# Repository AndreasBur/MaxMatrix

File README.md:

# MaxMatrix
This is a Arduino library for the MAX7219 and a LED dot matrix.

Features:

- set Char
- scroll text over the matrix
- set dot

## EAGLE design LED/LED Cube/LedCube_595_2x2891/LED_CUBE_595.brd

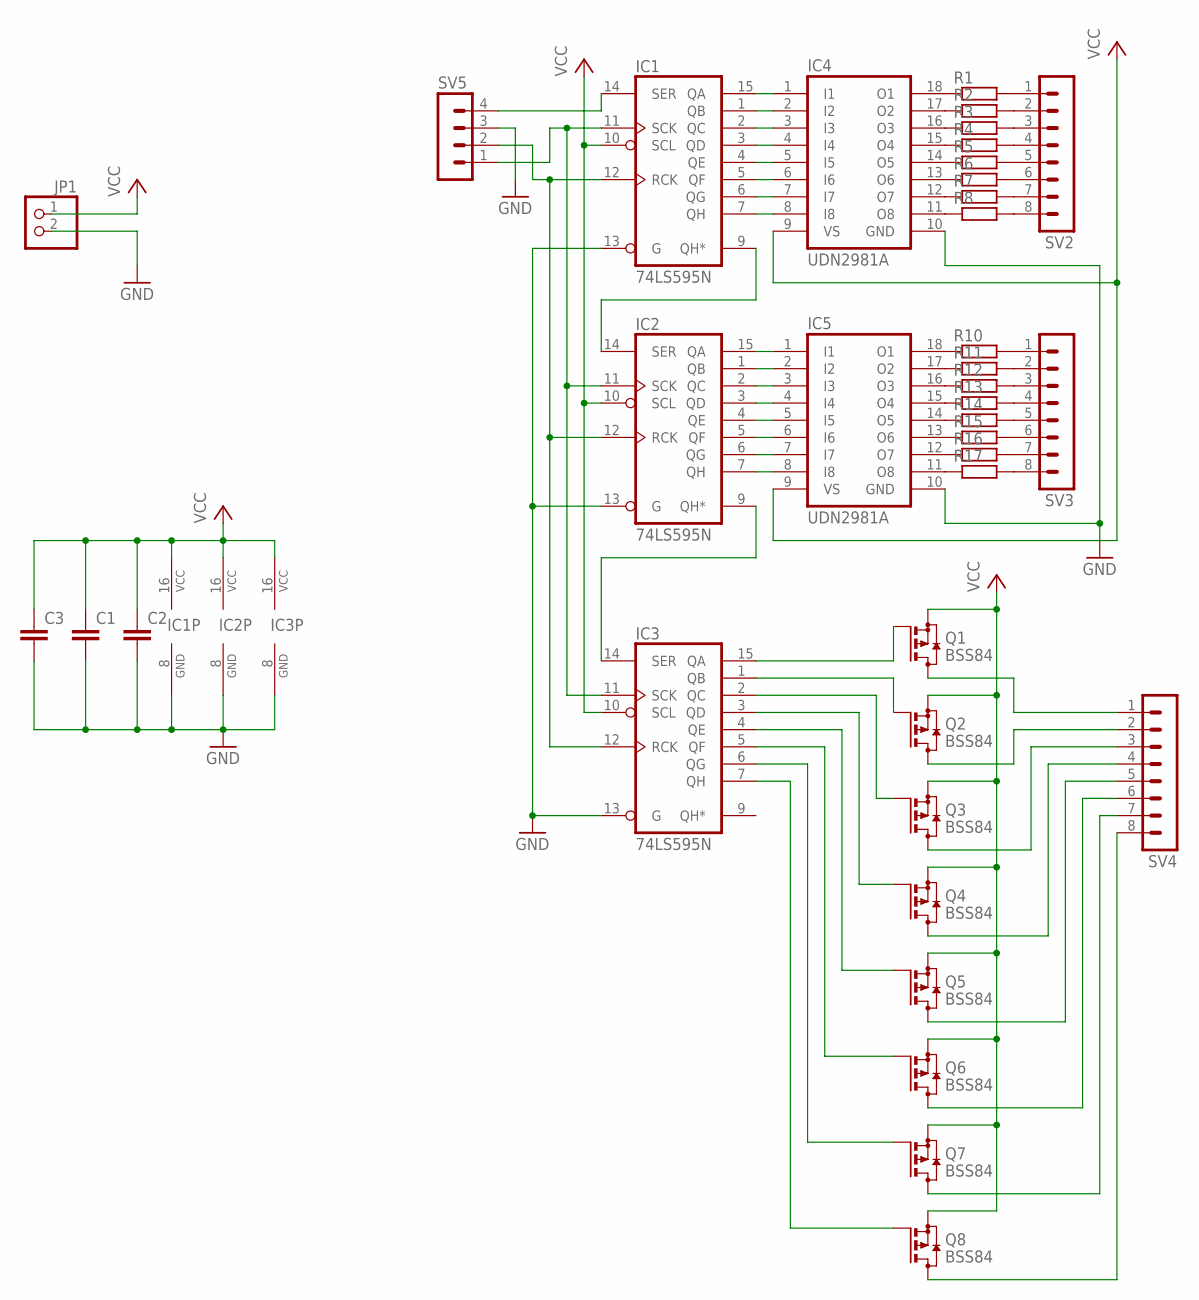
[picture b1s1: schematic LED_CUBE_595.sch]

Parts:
C1, C2, C3: C-EU025-025X050; C025-025X050
IC1, IC2, IC3: 74LS595N; DIL16
IC4, IC5: UDN2981A; DIL18
JP1: PINHD-1X2; 1X02
Q1, Q2, Q3, Q4, Q5, Q6, Q7, Q8: BSS84; SOT23
R1, R2, R3, R4, R5, R6, R7, R8, R10, R11, R12, R13, R14, R15, R16, R17: R-EU_0204/2V; 0204V
SV2, SV3, SV4: MA08-1
SV5: MA04-1

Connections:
GND: C1.2, C2.2, C3.2, IC1.8 (GND), IC1.13 (G), IC2.8 (GND), IC2.13 (G), IC3.8 (GND), IC3.13 (G), IC4.10 (GND), IC5.10 (GND), JP1.2, SV5.3
unnamed: IC1.9 (QH*), IC2.14 (SER)
unnamed: IC1.15 (QA), IC4.1 (I1)
unnamed: IC1.1 (QB), IC4.2 (I2)
unnamed: IC1.2 (QC), IC4.3 (I3)
unnamed: IC1.3 (QD), IC4.4 (I4)
unnamed: IC1.4 (QE), IC4.5 (I5)
unnamed: IC1.5 (QF), IC4.6 (I6)
unnamed: IC1.6 (QG), IC4.7 (I7)
unnamed: IC1.7 (QH), IC4.8 (I8)
unnamed: IC2.15 (QA), IC5.1 (I1)
unnamed: IC2.1 (QB), IC5.2 (I2)
unnamed: IC2.2 (QC), IC5.3 (I3)
unnamed: IC2.3 (QD), IC5.4 (I4)
unnamed: IC2.4 (QE), IC5.5 (I5)
unnamed: IC2.5 (QF), IC5.6 (I6)
unnamed: IC2.6 (QG), IC5.7 (I7)
unnamed: IC2.7 (QH), IC5.8 (I8)
unnamed: IC4.18 (O1), R1.1
unnamed: IC4.17 (O2), R2.1
unnamed: IC4.16 (O3), R3.1
unnamed: IC4.15 (O4), R4.1
unnamed: IC4.14 (O5), R5.1
unnamed: IC4.13 (O6), R6.1
unnamed: IC4.12 (O7), R7.1
unnamed: IC4.11 (O8), R8.1
unnamed: R1.2, SV2.1
unnamed: IC1.11 (SCK), IC2.11 (SCK), IC3.11 (SCK), SV5.1
unnamed: IC1.14 (SER), SV5.4
unnamed: IC1.12 (RCK), IC2.12 (RCK), IC3.12 (RCK), SV5.2
unnamed: IC2.9 (QH*), IC3.14 (SER)
unnamed: IC5.17 (O2), R11.1
unnamed: IC5.16 (O3), R12.1
unnamed: IC5.15 (O4), R13.1
unnamed: IC5.14 (O5), R14.1
unnamed: IC5.13 (O6), R15.1
unnamed: IC5.12 (O7), R16.1
unnamed: IC5.11 (O8), R17.1
unnamed: R2.2, SV2.2
unnamed: IC5.18 (O1), R10.1
unnamed: R3.2, SV2.3
unnamed: R4.2, SV2.4
unnamed: R5.2, SV2.5
unnamed: R6.2, SV2.6
unnamed: R7.2, SV2.7
unnamed: R8.2, SV2.8
unnamed: R10.2, SV3.1
unnamed: R11.2, SV3.2
unnamed: R12.2, SV3.3
unnamed: R13.2, SV3.4
unnamed: R14.2, SV3.5
unnamed: R15.2, SV3.6
unnamed: R16.2, SV3.7
unnamed: R17.2, SV3.8
unnamed: Q1.3 (D), SV4.1
unnamed: Q2.3 (D), SV4.2
unnamed: Q3.3 (D), SV4.3
unnamed: Q4.3 (D), SV4.4
unnamed: Q5.3 (D), SV4.5
unnamed: Q6.3 (D), SV4.6
unnamed: Q7.3 (D), SV4.7
unnamed: Q8.3 (D), SV4.8
unnamed: IC3.1 (QB), Q2.1 (G)
unnamed: IC3.2 (QC), Q3.1 (G)
unnamed: IC3.3 (QD), Q4.1 (G)
unnamed: IC3.4 (QE), Q5.1 (G)
unnamed: IC3.5 (QF), Q6.1 (G)
unnamed: IC3.6 (QG), Q7.1 (G)
unnamed: IC3.7 (QH), Q8.1 (G)
unnamed: IC3.15 (QA), Q1.1 (G)
VCC: C1.1, C2.1, C3.1, IC1.10 (SCL), IC1.16 (VCC), IC2.10 (SCL), IC2.16 (VCC), IC3.10 (SCL), IC3.16 (VCC), IC4.9 (VS), IC5.9 (VS), JP1.1, Q1.2 (S), Q2.2 (S), Q3.2 (S), Q4.2 (S), Q5.2 (S), Q6.2 (S), Q7.2 (S), Q8.2 (S)

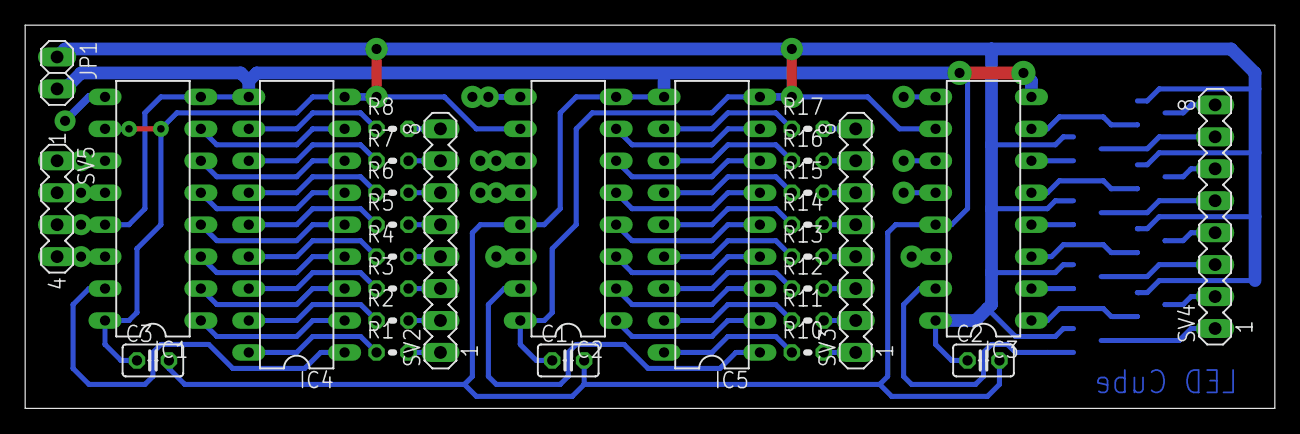
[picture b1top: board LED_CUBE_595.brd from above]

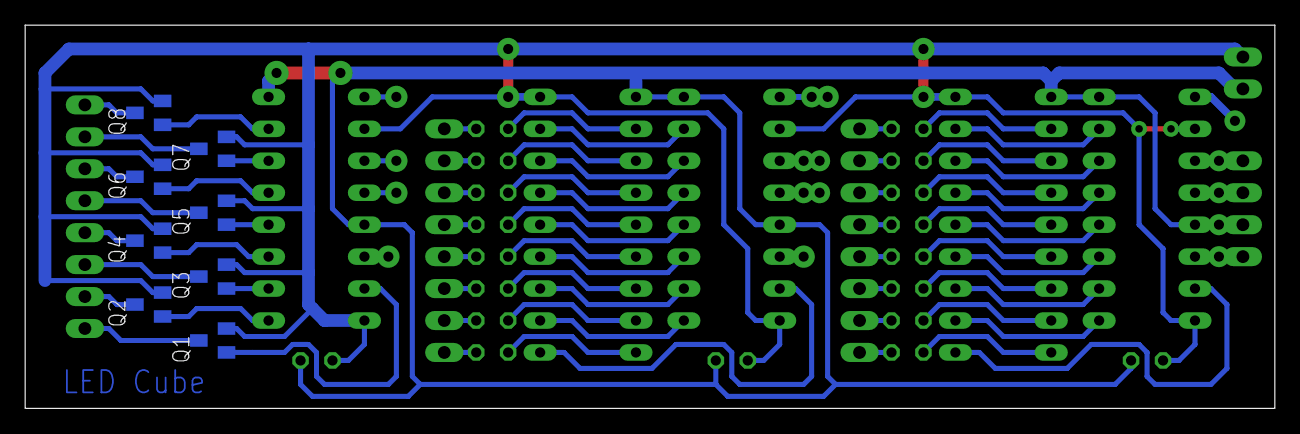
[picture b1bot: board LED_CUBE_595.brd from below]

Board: 2 copper layers, 99.4 x 30.5 mm, 37 parts (8 on the bottom side), 71 nets.

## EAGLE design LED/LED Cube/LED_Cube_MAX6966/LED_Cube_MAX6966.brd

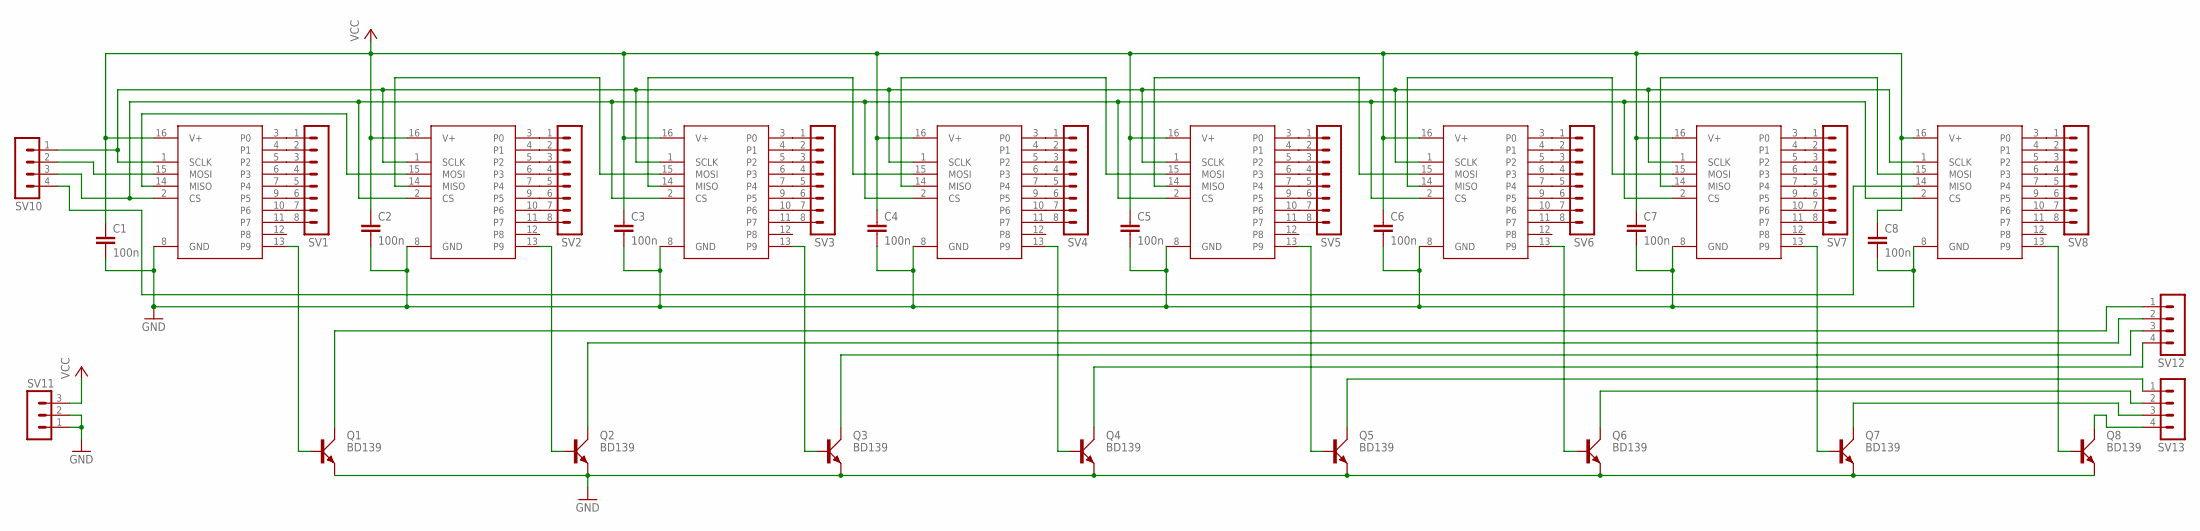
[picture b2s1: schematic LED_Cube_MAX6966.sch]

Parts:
C1, C2, C3, C4, C5, C6, C7, C8: 100n; C025_050-025X075
Q1, Q2, Q3, Q4, Q5, Q6, Q7, Q8: BD139; TO126AV
SV1, SV2, SV3, SV4, SV5, SV6, SV7, SV8: MA08-1
SV10, SV12, SV13: MA04-1
SV11: MA03-1
U$1, U$2, U$3, U$4, U$5, U$6, U$7, U$8: MAX6966; QSOP16

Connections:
GND: C1.2, C2.2, C3.2, C4.2, C5.2, C6.2, C7.2, C8.2, Q1.E, Q2.E, Q3.E, Q4.E, Q5.E, Q6.E, Q7.E, Q8.E, SV11.1, SV11.2, U$1.8 (GND), U$2.8 (GND), U$3.8 (GND), U$4.8 (GND), U$5.8 (GND), U$6.8 (GND), U$7.8 (GND), U$8.8 (GND)
unnamed: SV1.1, U$1.3 (P0)
unnamed: SV1.2, U$1.4 (P1)
unnamed: SV1.3, U$1.5 (P2)
unnamed: SV1.4, U$1.6 (P3)
unnamed: SV1.5, U$1.7 (P4)
unnamed: SV1.6, U$1.9 (P5)
unnamed: SV1.7, U$1.10 (P6)
unnamed: SV1.8, U$1.11 (P7)
unnamed: SV2.1, U$2.3 (P0)
unnamed: SV2.2, U$2.4 (P1)
unnamed: SV2.3, U$2.5 (P2)
unnamed: SV2.4, U$2.6 (P3)
unnamed: SV2.5, U$2.7 (P4)
unnamed: SV2.6, U$2.9 (P5)
unnamed: SV2.7, U$2.10 (P6)
unnamed: SV2.8, U$2.11 (P7)
unnamed: SV3.1, U$3.3 (P0)
unnamed: SV3.2, U$3.4 (P1)
unnamed: SV3.3, U$3.5 (P2)
unnamed: SV3.4, U$3.6 (P3)
unnamed: SV3.5, U$3.7 (P4)
unnamed: SV3.6, U$3.9 (P5)
unnamed: SV3.7, U$3.10 (P6)
unnamed: SV3.8, U$3.11 (P7)
unnamed: SV4.1, U$4.3 (P0)
unnamed: SV4.2, U$4.4 (P1)
unnamed: SV4.3, U$4.5 (P2)
unnamed: SV4.4, U$4.6 (P3)
unnamed: SV4.5, U$4.7 (P4)
unnamed: SV4.6, U$4.9 (P5)
unnamed: SV4.7, U$4.10 (P6)
unnamed: SV4.8, U$4.11 (P7)
unnamed: SV5.1, U$5.3 (P0)
unnamed: SV5.2, U$5.4 (P1)
unnamed: SV5.3, U$5.5 (P2)
unnamed: SV5.4, U$5.6 (P3)
unnamed: SV5.5, U$5.7 (P4)
unnamed: SV5.6, U$5.9 (P5)
unnamed: SV5.7, U$5.10 (P6)
unnamed: SV5.8, U$5.11 (P7)
unnamed: SV6.1, U$6.3 (P0)
unnamed: SV6.2, U$6.4 (P1)
unnamed: SV6.3, U$6.5 (P2)
unnamed: SV6.4, U$6.6 (P3)
unnamed: SV6.5, U$6.7 (P4)
unnamed: SV6.6, U$6.9 (P5)
unnamed: SV6.7, U$6.10 (P6)
unnamed: SV6.8, U$6.11 (P7)
unnamed: SV7.1, U$7.3 (P0)
unnamed: SV7.2, U$7.4 (P1)
unnamed: SV7.3, U$7.5 (P2)
unnamed: SV7.4, U$7.6 (P3)
unnamed: SV7.5, U$7.7 (P4)
unnamed: SV7.6, U$7.9 (P5)
unnamed: SV7.7, U$7.10 (P6)
unnamed: SV7.8, U$7.11 (P7)
unnamed: SV8.1, U$8.3 (P0)
unnamed: SV8.2, U$8.4 (P1)
unnamed: SV8.3, U$8.5 (P2)
unnamed: SV8.4, U$8.6 (P3)
unnamed: SV8.5, U$8.7 (P4)
unnamed: SV8.6, U$8.9 (P5)
unnamed: SV8.7, U$8.10 (P6)
unnamed: SV8.8, U$8.11 (P7)
unnamed: U$4.14 (MISO), U$5.15 (MOSI)
unnamed: Q8.B, U$8.13 (P9)
unnamed: SV10.3, U$1.2 (CS), U$2.2 (CS), U$3.2 (CS), U$4.2 (CS), U$5.2 (CS), U$6.2 (CS), U$7.2 (CS), U$8.2 (CS)
unnamed: Q7.B, U$7.13 (P9)
unnamed: Q6.B, U$6.13 (P9)
unnamed: Q5.B, U$5.13 (P9)
unnamed: Q4.B, U$4.13 (P9)
unnamed: Q3.B, U$3.13 (P9)
unnamed: Q2.B, U$2.13 (P9)
unnamed: Q1.B, U$1.13 (P9)
unnamed: Q8.C, SV13.4
unnamed: Q7.C, SV13.3
unnamed: SV10.1, U$1.1 (SCLK), U$2.1 (SCLK), U$3.1 (SCLK), U$4.1 (SCLK), U$5.1 (SCLK), U$6.1 (SCLK), U$7.1 (SCLK), U$8.1 (SCLK)
unnamed: Q6.C, SV13.2
unnamed: Q5.C, SV13.1
unnamed: Q4.C, SV12.4
unnamed: Q3.C, SV12.3
unnamed: Q2.C, SV12.2
unnamed: Q1.C, SV12.1
unnamed: U$1.14 (MISO), U$2.15 (MOSI)
unnamed: SV10.2, U$1.15 (MOSI)
unnamed: U$2.14 (MISO), U$3.15 (MOSI)
unnamed: U$3.14 (MISO), U$4.15 (MOSI)
unnamed: U$7.14 (MISO), U$8.15 (MOSI)
unnamed: U$5.14 (MISO), U$6.15 (MOSI)
unnamed: U$6.14 (MISO), U$7.15 (MOSI)
unnamed: SV10.4, U$8.14 (MISO)
VCC: C1.1, C2.1, C3.1, C4.1, C5.1, C6.1, C7.1, C8.1, SV11.3, U$1.16 (V+), U$2.16 (V+), U$3.16 (V+), U$4.16 (V+), U$5.16 (V+), U$6.16 (V+), U$7.16 (V+), U$8.16 (V+)

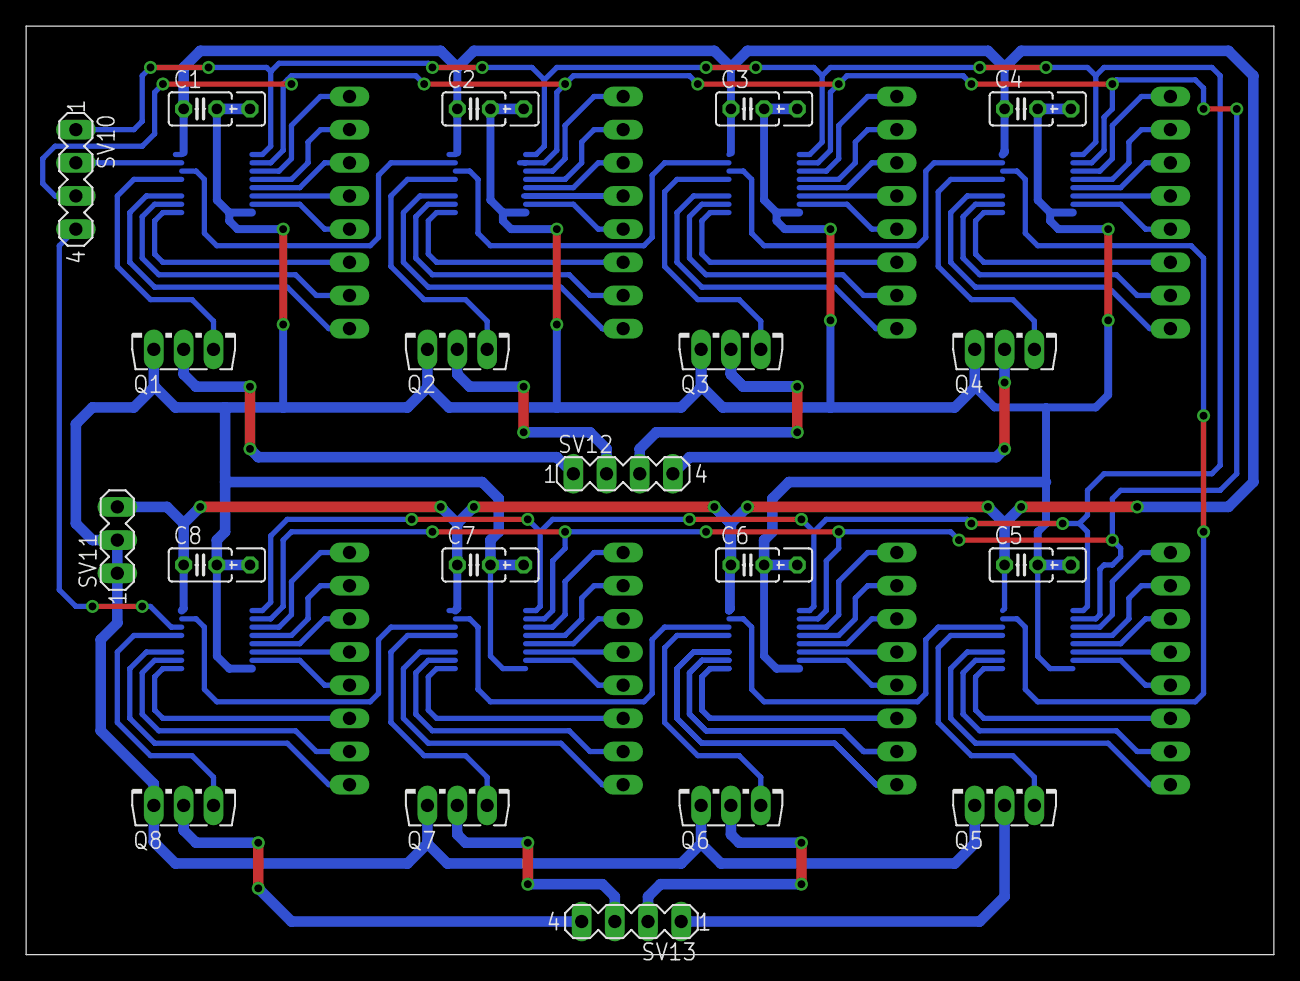
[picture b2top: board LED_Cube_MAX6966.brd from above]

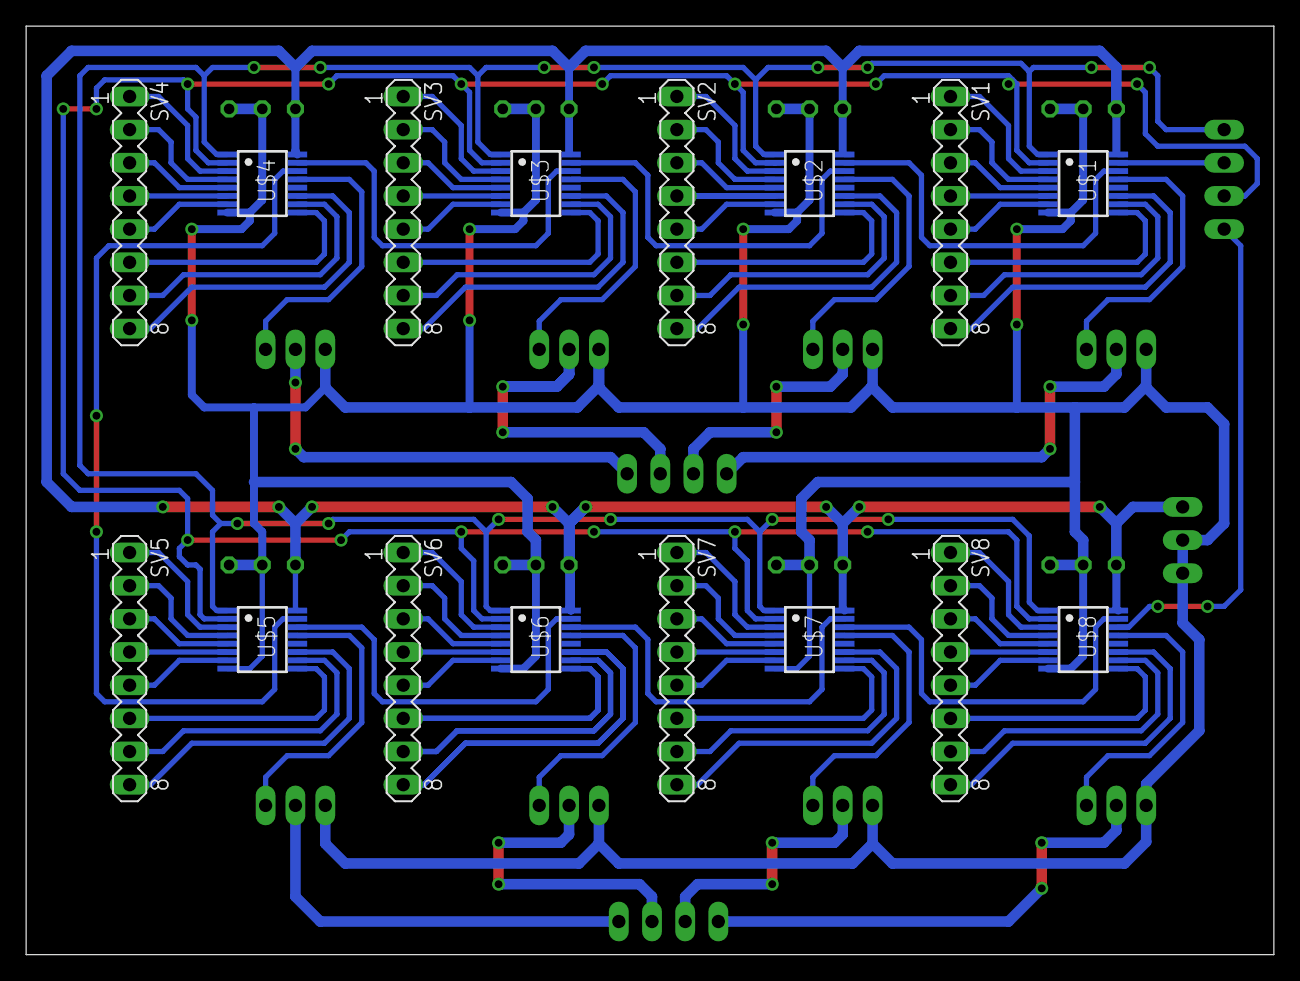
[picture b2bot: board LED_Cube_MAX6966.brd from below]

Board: 2 copper layers, 95.6 x 71.1 mm, 36 parts (16 on the bottom side), 93 nets.

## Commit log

2016-06-23 Add MaxMatrix files
2016-06-27 Example sketch for MaxMatrix library
2016-06-28 change folder structure
2016-11-01 added dokumentation
2016-11-02 - added whole project
2016-11-02 deleted eclipse file
2016-11-02 Led Matrix C# control tool
2016-11-02 uncomment not used type
2016-11-02 - added StandardTypes - some corrections
2016-11-02 - complete rebuild
2016-11-02 -added picture
2016-11-02 added C# tool Windows Forms
2016-11-02 - Todo added
2016-11-03 changed format of picture
2016-11-04 - extended MaxMatrix space between chars - added comments
2016-11-04 - TimerTwo changed Bit write
2016-11-05 - added ArrayDrehen CBP
2016-11-06 added space between chars
2016-11-07 modified textbox settings
2016-11-09 added comments
2016-11-11 support for win7
2016-11-11 added comment
2016-11-11 changed button width
2016-11-18 added LED
2016-11-20 replaced tabs
2016-11-21 added TimerTwo CTC and PWM mode
2016-11-22 ignore some atmel studio files
2016-11-22 added gitignore file
2016-11-22 delted
2016-11-22 added no orientation
2016-11-22 changed structure
2016-11-22 added pin connection
2016-11-22 modified comment
2016-11-22 deleted old profect
2016-11-23 deleted example folder
2016-11-23 changed location of example folder
2016-11-26 ...
    ...
2016-11-30 changed variable names in setSprite function
2017-01-09 added led cube project from mikrocontroller.net
2017-01-11 added new Led Cube project from mikrocontroller.net
2017-01-17 changed datatypes fixed getRowLL call to getRow
2017-03-31 deleted installer
2017-03-31 -added space between chars function
2017-03-31 renamed doku
2017-03-31 updated picture path
2017-03-31 - edited picture
2017-06-30 added volatile
2017-09-19 - update of standard types
2021-02-11 Removed unusred types
